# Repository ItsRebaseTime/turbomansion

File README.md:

# turbomansion

Hello, welcome to the turbomansion repository.

## The name

First let's start with the name - turbomansion.
The word comes from a few places in pop culture history but for me it got stuck in my head because of the legendary looter-shooter video game series - Borderlands, made by 2K and Gearbox. "Turbomansion" is mentioned in Borderlands The Pre-Sequel during mission "Lost Legion Invasion" as seen in this [video](https://www.youtube.com/watch?v=5qd0URBWsjE).

## The idea

Main goal of this project is to create a fully open source smart home units library. Of course nothing is perfect and so is this project, some things may deviate from the ultimate goal and some compromises will be made but I will be happy and I hope anyone who reads this would feel the same if the project does not deviate too far from these values:

* Open source documentation, plans, files, code, etc.
* Easily obtainable materials all over the world
* Low cost and low effort
* Ease of deployment
* Ease of use
* Ease of maintenance and repair
* Customizability
* No proprietary bullshit
* No manufacturer cloud connectivity (unless you want to (trust me - you don't))
* Complete control with Home Assistant

## Units

### Multisensor

[Multisensor](/units/multisensor/README.md) - An all-in-one solution for your home monitoring and automation needs.

### Control panel

[Control panel](/units/control_panel/README.md) - An awesome home automation dashboard/control panel.

### PoE roller blinds

[PoE roller blinds](/units/roller_blinds/README.md) - Smart and automated PoE powered roller blinds.

### DT82TV curtain motor controller

[DT82TV curtain motor controller](/units/rs485_dooya_curtain_controller/README.md) - RS485 controller setup for Dooya DT82TV curtain motors with ESPHome.

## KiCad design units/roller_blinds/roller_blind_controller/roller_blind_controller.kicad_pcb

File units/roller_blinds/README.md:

# PoE Roller Blinds

## Introduction

During my smart home development I was searching for smart PoE-powered black-out roller blinds and to my surprise I was not able to find anything remotely affordable and compatible with my home assistant setup.

There are a few offerings in the industry but they have their own downsides:

| Product                                                                                                                         | Features                                                                                                                 | Antifeatures                                                                                                                                         |
|---------------------------------------------------------------------------------------------------------------------------------|--------------------------------------------------------------------------------------------------------------------------|------------------------------------------------------------------------------------------------------------------------------------------------------|
| [Powershades TruePoE](https://powershades.com/truepoe)                                                                          | All-in-one solution, easy to deploy                                                                                      | Cloud-based, unrepairable (no available parts), not sold in EU                                                                                       |
| [Somfy Sonesse® 30 PoE (and other variations)](https://www.somfysystems.com/en-us/products/1241147/sonesse-30-poe)              | All-in-one solution, easy to deploy                                                                                      | Too expensive (400 eur), unrepairable (no available parts), proprietary control interface                                                            |
| [Smart wings hardwired PoE roller blinds](https://www.smartwingshome.com/pages/the-worlds-first-poe-matter-over-ethernet-motor) | All-in-one solution, easy to deploy, optional PoE and DC power, compatible with Home Assistant and Matter out of the box | The motor itself is 170eur, unrepairable (no available parts), but it is still the best solution if you want plug and play PoE powered roller blinds |

## Features

| Feature      | Specifications                                                      | Note     |
|--------------|---------------------------------------------------------------------|----------|
| PoE          | 802.3af, 6W                                                         |          |
| Ethernet     | 802.3-2008, 10/100Mbps                                              |          |
| WiFi         | 802.11b/g/n, 150Mbps                                                | Optional |
| Bluetooth    | Bluetooth v4.2 BR/EDR and Bluetooth LE                              | Optional |
| Motor driver | TMC2209, silent, sensor-less homing, speed and acceleration control |          |

## Main parts

| Part                                      | Datasheet                                                                   | EU Shop                                                                                                         |
|-------------------------------------------|-----------------------------------------------------------------------------|-----------------------------------------------------------------------------------------------------------------|
| M5Stack PoE ESP32                         | [link](/units/roller_blinds/assets/docs/poesp32.pdf)                        | [link](https://eu.mouser.com/ProductDetail/M5Stack/U138?qs=vvQtp7zwQdPAxf%252BUv9YNIg%3D%3D)                    |
| FYSETC TMC2209 V3/V4 stepper motor driver | [link](/units/roller_blinds/assets/docs/Silent2209%20-%20FYSETC%20WIKI.pdf) | [link](https://www.amazon.de/-/en/Printer-Upgrade-Microsteps-Motherboard-Controller/dp/B07Z8QP8M9/ref=sr_1_3)   |
| 2.54mm female header kit                  |                                                                             | [link](https://www.amazon.de/-/en/Straight-Connector-Assortment-Arduino-Prototype/dp/B07Q1XBGFB/ref=sr_1_2)     |
| M3 screw kit                              |                                                                             | [link](https://www.amazon.de/-/en/Countersunk-Stainless-Phillips-Assortment-Threaded/dp/B0DPKYXVWY/ref=sr_1_15) |
| M4 screw kit                              |                                                                             | [link](https://www.amazon.de/-/en/Countersunk-Stainless-Phillips-Assortment-Threaded/dp/B0DPL17F6X/ref=sr_1_15) |
| 8x2 round magnets                         |                                                                             | [link](https://www.amazon.de/-/en/Aenienoe-Magnets-Neodymium-Magnetic-Whiteboard/dp/B0DDBQJ7TM/ref=sr_1_5)      |

## 3D printed parts

| Part                | File                                                                          | Note                                                                                          |
|---------------------|-------------------------------------------------------------------------------|-----------------------------------------------------------------------------------------------|
| Motor mount         | [file](/units/roller_blinds/assets/cad_files/for_printing/28byj-48_mount.3mf) | Holds the motor                                                                               |
| Spring mount        | [file](/units/roller_blinds/assets/cad_files/for_printing/spring_mount.3mf)   | Holds the spring assembly                                                                     |
| Motor shaft adapter | [file](/units/roller_blinds/assets/cad_files/for_printing/motor_adapter.3mf)  | Adapts the motor shaft to the aluminium extrusion of the roller blind                         |
| Motor cover         | [file](/units/roller_blinds/assets/cad_files/for_printing/motor_cover.3mf)    | Holds the electronics and can be used to cover up the other side too if you like the symmetry |

## Optional parts

| Part                                     | Datasheet                                                                     | EU Shop                                                                                                  | Note                                                |
|------------------------------------------|-------------------------------------------------------------------------------|----------------------------------------------------------------------------------------------------------|-----------------------------------------------------|
| 2.4GHz BT/Wifi flexible adhesive antenna | [link](/units/roller_blinds/assets/Amphenol_04262021_PIOV0MSNRBA-2306519.pdf) | [link](https://eu.mouser.com/ProductDetail/Amphenol-SAA/PIOV0MSNRBA-100?qs=GedFDFLaBXF5eAFxhrTnpw%3D%3D) | Can enable Bluetooth functionality for various uses |

## Electronics

The electronics assembly is based on M5Stack PoE ESP32 module:

When opened it will contain 2 PCBs connected via 2x5 pin header. The PCB with the RJ45 port and ESP32 module will be used as the main board for this project, the other PCB will be dismantled for the PoE module.

The complete assembly could be done with a perforated soldering board and a few wires, but since we do things proper-ish around here - the printed circuit board was designed:

## Motor preparation

The 28BYJ-48 unipolar motor is designed to be controlled with simpler logic, for example shift registers and contains the center taps of both of the coils connected to the 5th pin in the connector:

This makes the motor unusable with regular bipolar motor drivers like TMC2209. Luckily there is a simple modification to convert 28BYJ-48 to bipolar operation.

### The modification

You will need to take off the blue plastic cover from the side of the motor to reveal a small PCB with all the electrical connections of the motor. Then cut the center trace. I have done it with a rotary tool, but a sharp knife would work nicely too.

### Before

### After

Now the motor will work with any common stepper motor driver.

## Driver

The 28BYJ-48 motor is designed to take full 5V current on half of its coil. After the modification we technically doubled the coil resistance and can crank the TMC2209 driver current all the way up with the on-board potentiometer. I used FYSETC TMC2209 V4.0 driver boards so for me the potentiometer should be turned all the way clockwise.

> [!NOTE]
> If you are using any other TMC2209 driver - double check the RX, TX, INDEX, and DIAG pin positions, they differ from driver to driver and you may need to creatively add 1k resistor between RX and TX pins on the board. Also some of the boards have VREF, DIAG, and INDEX pins switched around. PCB only supports driver boards which have INDEX and DIAG pins at 90 degrees from the other pins.

## Electronics assembly

The complete electronics assembly looks like this:

## Mechanical assembly

And the complete mechanical assembly looks like this:

## ESPHome configuration

```
esphome:
  name: blinds
  friendly_name: Blinds
  on_boot:
    - tmc2209.configure:
        microsteps: 1
        interpolation: True
        enable_spreadcycle: False
        tcool_threshold: 1000 # SG can be triggered when speed exceeds this value
    - tmc2209.stallguard:
        threshold: 5 # SG is triggered if the SG value is lower than 2x threshold
    - tmc2209.currents:
        standstill_mode: normal # coil_short_ls
        irun: 31 # 16 for best microstep performance (16/32 = 1/2 maximum motor current)
        ihold: 16 # should be 0 to enable passive breaking
        tpowerdown: 0
        iholddelay: 0
    - button.press: home_button # home right after boot

esp32:
  board: esp32dev
  framework:
    type: arduino
    
# Enable logging
logger:
  hardware_uart: UART2

# Enable Home Assistant API
api:
  encryption:
    key: "xxxxxxxxxxxxxxxxxxxxxxxxxx"

ota:
  - platform: esphome
    password: "xxxxxxxxxxxxxxxxxxxxxxxxxxxxxxxxx"

ethernet:
  type: IP101
  mdc_pin: GPIO23
  mdio_pin: GPIO18
  clk_mode: GPIO0_IN
  phy_addr: 1
  power_pin: GPIO5

text_sensor:
  - platform: ethernet_info
    ip_address:
      name: "IP"
    mac_address:
      name: "MAC"
    dns_address:
      name: "DNS"

external_components:
  - source: github://slimcdk/esphome-custom-components
    components: [ tmc2209_hub, tmc2209, stepper ]

globals:
  - id: has_homed
    type: bool
    initial_value: "true"
    restore_value: False
  - id: blinds_bottom_pos
    type: int
    initial_value: '9999'
    restore_value: True
  - id: blinds_top_pos
    type: int
    initial_value: '0'
    restore_value: True

uart:
  id: tmc2209_uart
  rx_pin: GPIO1
  tx_pin: GPIO3
  baud_rate: 500000
  
tmc2209_hub:
  id: tmc_hub
  uart_id: tmc2209_uart

stepper:
  - platform: tmc2209
    id: driver
    tmc2209_hub_id: tmc_hub
    diag_pin: GPIO17
    index_pin: GPIO16
    max_speed: 50 steps/s
    acceleration: 20 steps/s^2
    deceleration: 20 steps/s^2
    address: 0x00
    # rsense: 110 mOhm
    vsense: False
    on_status:
      - logger.log:
          format: "Driver is reporting an update! (code %d)"
          args: ["code"]
      - if:
          condition:
            lambda: return code == tmc2209::DIAG_TRIGGERED;
          then:
            - logger.log: DIAG_TRIGGERED
      - if:
          condition:
            lambda: return code == tmc2209::DIAG_TRIGGER_CLEARED;
          then:
            - logger.log: DIAG_TRIGGER_CLEARED
      - if:
          condition:
            lambda: return code == tmc2209::RESET;
          then:
            - logger.log: RESET
      - if:
          condition:
            lambda: return code == tmc2209::RESET_CLEARED;
          then:
            - logger.log: RESET_CLEARED
      - if:
          condition:
            lambda: return code == tmc2209::DRIVER_ERROR;
          then:
            - logger.log: DRIVER_ERROR
      - if:
          condition:
            lambda: return code == tmc2209::DRIVER_ERROR_CLEARED;
          then:
            - logger.log: DRIVER_ERROR_CLEARED
      - if:
          condition:
            lambda: return code == tmc2209::CP_UNDERVOLTAGE;
          then:
            - logger.log: CP_UNDERVOLTAGE
      - if:
          condition:
            lambda: return code == tmc2209::CP_UNDERVOLTAGE_CLEARED;
          then:
            - logger.log: CP_UNDERVOLTAGE_CLEARED
      - if:
          condition:
            lambda: return code == tmc2209::OVERTEMPERATURE_PREWARNING;
          then:
            - logger.log: OVERTEMPERATURE_PREWARNING
      - if:
          condition:
            lambda: return code == tmc2209::OVERTEMPERATURE_PREWARNING_CLEARED;
          then:
            - logger.log: OVERTEMPERATURE_PREWARNING_CLEARED
      - if:
          condition:
            lambda: return code == tmc2209::OVERTEMPERATURE;
          then:
            - logger.log: OVERTEMPERATURE
      - if:
          condition:
            lambda: return code == tmc2209::OVERTEMPERATURE_CLEARED;
          then:
            - logger.log: OVERTEMPERATURE_CLEARED
      - if:
          condition:
            lambda: return code == tmc2209::TEMPERATURE_ABOVE_120C;
          then:
            - logger.log: TEMPERATURE_ABOVE_120C
      - if:
          condition:
            lambda: return code == tmc2209::TEMPERATURE_BELOW_120C;
          then:
            - logger.log: TEMPERATURE_BELOW_120C
      - if:
          condition:
            lambda: return code == tmc2209::TEMPERATURE_ABOVE_143C;
          then:
            - logger.log: TEMPERATURE_ABOVE_143C
      - if:
          condition:
            lambda: return code == tmc2209::TEMPERATURE_BELOW_143C;
          then:
            - logger.log: TEMPERATURE_BELOW_143C
      - if:
          condition:
            lambda: return code == tmc2209::TEMPERATURE_ABOVE_150C;
          then:
            - logger.log: TEMPERATURE_ABOVE_150C
      - if:
          condition:
            lambda: return code == tmc2209::TEMPERATURE_BELOW_150C;
          then:
            - logger.log: TEMPERATURE_BELOW_150C
      - if:
          condition:
            lambda: return code == tmc2209::TEMPERATURE_ABOVE_157C;
          then:
            - logger.log: TEMPERATURE_ABOVE_157C
      - if:
          condition:
            lambda: return code == tmc2209::TEMPERATURE_BELOW_157C;
          then:
            - logger.log: TEMPERATURE_BELOW_157C
      - if:
          condition:
            lambda: return code == tmc2209::OPEN_LOAD;
          then:
            - logger.log: OPEN_LOAD
      - if:
          condition:
            lambda: return code == tmc2209::OPEN_LOAD_CLEARED;
          then:
            - logger.log: OPEN_LOAD_CLEARED
      - if:
          condition:
            lambda: return code == tmc2209::OPEN_LOAD_A;
          then:
            - logger.log: OPEN_LOAD_A
      - if:
          condition:
            lambda: return code == tmc2209::OPEN_LOAD_A_CLEARED;
          then:
            - logger.log: OPEN_LOAD_A_CLEARED
      - if:
          condition:
            lambda: return code == tmc2209::OPEN_LOAD_B;
          then:
            - logger.log: OPEN_LOAD_B
      - if:
          condition:
            lambda: return code == tmc2209::OPEN_LOAD_B_CLEARED;
          then:
            - logger.log: OPEN_LOAD_B_CLEARED
      - if:
          condition:
            lambda: return code == tmc2209::LOW_SIDE_SHORT;
          then:
            - logger.log: LOW_SIDE_SHORT
      - if:
          condition:
            lambda: return code == tmc2209::LOW_SIDE_SHORT_CLEARED;
          then:
            - logger.log: LOW_SIDE_SHORT_CLEARED
      - if:
          condition:
            lambda: return code == tmc2209::LOW_SIDE_SHORT_A;
          then:
            - logger.log: LOW_SIDE_SHORT_A
      - if:
          condition:
            lambda: return code == tmc2209::LOW_SIDE_SHORT_A_CLEARED;
          then:
            - logger.log: LOW_SIDE_SHORT_A_CLEARED
      - if:
          condition:
            lambda: return code == tmc2209::LOW_SIDE_SHORT_B;
          then:
            - logger.log: LOW_SIDE_SHORT_B
      - if:
          condition:
            lambda: return code == tmc2209::LOW_SIDE_SHORT_B_CLEARED;
          then:
            - logger.log: LOW_SIDE_SHORT_B_CLEARED
      - if:
          condition:
            lambda: return code == tmc2209::GROUND_SHORT;
          then:
            - logger.log: GROUND_SHORT
      - if:
          condition:
            lambda: return code == tmc2209::GROUND_SHORT_CLEARED;
          then:
            - logger.log: GROUND_SHORT_CLEARED
      - if:
          condition:
            lambda: return code == tmc2209::GROUND_SHORT_A;
          then:
            - logger.log: GROUND_SHORT_A
      - if:
          condition:
            lambda: return code == tmc2209::GROUND_SHORT_A_CLEARED;
          then:
            - logger.log: GROUND_SHORT_A_CLEARED
      - if:
          condition:
            lambda: return code == tmc2209::GROUND_SHORT_B;
          then:
            - logger.log: GROUND_SHORT_B
      - if:
          condition:
            lambda: return code == tmc2209::GROUND_SHORT_B_CLEARED;
          then:
            - logger.log: GROUND_SHORT_B_CLEARED
    on_stall:
      - logger.log: "Motor stalled!"
      - if:
          condition:
            lambda: |-
              return !id(has_homed);
          then:
            - stepper.stop: driver
            - stepper.report_position:
                id: driver
                position: 0
            - stepper.set_target:
                id: driver
                target: 0
            - globals.set:
                id: has_homed
                value: "true"
            - logger.log: "Homed"

button:
  - platform: template
    entity_category: DIAGNOSTIC
    id: home_button
    name: "Home"
    on_press:
      - logger.log: "Going home!"
      - globals.set:
          id: has_homed
          value: "false"
      - stepper.set_target:
          id: driver
          target: -9999999

  - platform: template
    entity_category: DIAGNOSTIC
    id: set_bottom_pos_button
    name: "Set bottom position"
    on_press:
      then:
        - globals.set: 
            id: blinds_bottom_pos
            value: !lambda 'return id(driver)->current_position;'
        - lambda: |-
            ESP_LOGD("Blinds", "Setting bottom position to: %d", id(driver)->current_position);

  - platform: template
    entity_category: DIAGNOSTIC
    id: set_top_pos_button
    name: "Set top position"
    on_press:
      then:
        - globals.set: 
            id: blinds_top_pos
            value: !lambda 'return id(driver)->current_position;'
        - lambda: |-
            ESP_LOGD("Blinds", "Setting top position to: %d", id(driver)->current_position);

  - platform: template
    entity_category: DIAGNOSTIC
    name: "10 Steps forward"
    on_press:
      - stepper.set_target:
          id: driver
          target: !lambda 'return id(driver)->current_position +10;'

  - platform: template
    entity_category: DIAGNOSTIC
    name: "10 Steps backward"
    on_press:
      - stepper.set_target:
          id: driver
          target: !lambda 'return id(driver)->current_position -10;'

  - platform: template
    entity_category: DIAGNOSTIC
    name: "100 Steps forward"
    on_press:
      - stepper.set_target:
          id: driver
          target: !lambda 'return id(driver)->current_position +100;'

  - platform: template
    entity_category: DIAGNOSTIC
    name: "100 Steps backward"
    on_press:
      - stepper.set_target:
          id: driver
          target: !lambda 'return id(driver)->current_position -100;'

  - platform: template
    entity_category: DIAGNOSTIC
    name: "1000 Steps forward"
    on_press:
      - stepper.set_target:
          id: driver
          target: !lambda 'return id(driver)->current_position +1000;'

  - platform: template
    entity_category: DIAGNOSTIC
    name: "1000 Steps backward"
    on_press:
      - stepper.set_target:
          id: driver
          target: !lambda 'return id(driver)->current_position -1000;'

  - platform: template
    name: Stop
    on_press:
      - stepper.stop: driver

  - platform: restart
    name: "Restart"

cover:
  - platform: template
    device_class: blind
    id: blinds
    name: "Blinds"
    optimistic: False
    has_position: True

    lambda: |-
      #define MAP_FLOAT(x, in_min, in_max, out_min, out_max) ((float)(x - in_min) * (out_max - out_min) / (float)(in_max - in_min) + out_min)
      return MAP_FLOAT(id(stepper_position_sensor)->state, id(blinds_top_pos), id(blinds_bottom_pos), 1.0, 0.0);
    open_action:
      - if:
          condition:
            lambda: |-
              return id(has_homed);
          then:
            - stepper.set_target: 
                id: driver
                target: !lambda 'return id(blinds_top_pos);'
    close_action:
      - if:
          condition:
            lambda: |-
              return id(has_homed);
          then:
            - stepper.set_target: 
                id: driver
                target: !lambda 'return id(blinds_bottom_pos);'
    stop_action: 
      then:
        - stepper.stop: driver
    position_action: 
      - if:
          condition:
            lambda: |-
              return id(has_homed);
          then:
            - stepper.set_target: 
                id: driver
                target: !lambda |-
                  #define MAP_FLOAT(x, in_min, in_max, out_min, out_max) ((float)(x - in_min) * (out_max - out_min) / (float)(in_max - in_min) + out_min)
                  int pos_to_set = MAP_FLOAT(pos, 0.0, 1.0, id(blinds_bottom_pos), id(blinds_top_pos));
                  ESP_LOGD("Blinds", "Rolling blinds to: %d (%f)", pos_to_set, pos);
                  return pos_to_set;
        
binary_sensor:
  - platform: template
    id: homed_status_sensor
    entity_category: DIAGNOSTIC
    name: "Homed status"
    lambda: |-
      return id(has_homed);

sensor:
  - platform: template
    entity_category: DIAGNOSTIC
    id: top_position_sensor
    name: "Top position"
    accuracy_decimals: 0
    unit_of_measurement: "steps"
    filters:
      - delta: 1
    lambda: |-
      return id(blinds_top_pos);

  - platform: template
    entity_category: DIAGNOSTIC
    id: bottom_position_sensor
    name: "Bottom position"
    accuracy_decimals: 0
    unit_of_measurement: "steps"
    filters:
      - delta: 1
    lambda: |-
      return id(blinds_bottom_pos);

  - platform: template
    entity_category: DIAGNOSTIC
    id: stepper_position_sensor
    name: "Position"
    unit_of_measurement: "steps"
    accuracy_decimals: 0
    update_interval: 1s
    filters:
      - delta: 1
    lambda: |-
      return id(driver)->current_position;

  - platform: tmc2209
    entity_category: DIAGNOSTIC
    internal: True
    type: stallguard_result
    name: Driver stallguard
    update_interval: 250ms
    filters:
      - delta: 1

  # - platform: tmc2209
  #   entity_category: DIAGNOSTIC
  #   type: motor_load
  #   name: Motor load
  #   update_interval: 250ms

  # - platform: tmc2209
  #   type: actual_current
  #   name: Actual current
  #   update_interval: 250ms

  # - platform: tmc2209
  #   type: pwm_scale_sum
  #   name: PWM Scale Sum
  #   update_interval: 250ms

  # - platform: tmc2209
  #   type: pwm_scale_auto
  #   name: PWM Scale Auto
  #   update_interval: 250ms

  # - platform: tmc2209
  #   type: pwm_ofs_auto
  #   name: PWM OFS Auto
  #   update_interval: 250ms

  # - platform: tmc2209
  #   type: pwm_grad_auto
  #   name: PWM Grad Auto
  #   update_interval: 250ms

```

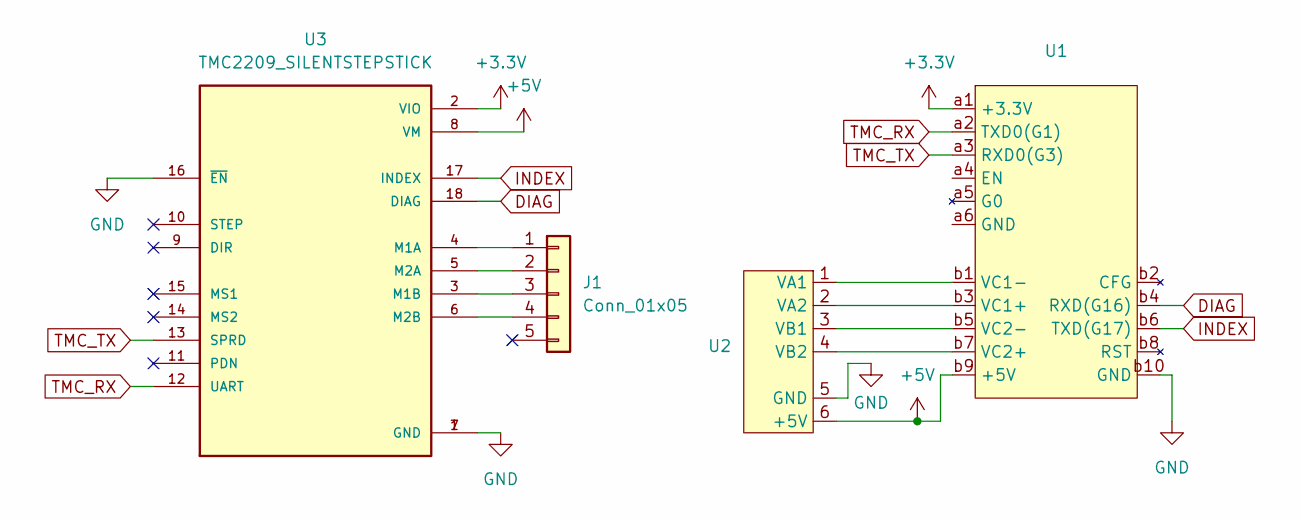
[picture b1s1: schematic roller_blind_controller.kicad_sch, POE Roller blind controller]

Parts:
J1: Conn_01x05; JST_XH_B5B-XH-A_1x05_P2.50mm_Vertical
U1: M5Stack_POE_base
U2: M5Stack_POE_module
U3: TMC2209_SILENTSTEPSTICK; MODULE_TMC2209_SILENTSTEPSTICK; PARTREV 1.20

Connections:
+3.3V: U1.a1 (+3.3V), U3.2 (VIO)
+5V: U1.b9 (+5V), U2.6 (+5V), U3.8 (VM)
DIAG: U1.b4 (RXD(G16)), U3.18 (DIAG)
GND: U1.b10 (GND), U2.5 (GND), U3.1 (GND), U3.7 (GND), U3.16 (~EN)
INDEX: U1.b6 (TXD(G17)), U3.17 (INDEX)
unnamed: J1.1, U3.4 (M1A)
unnamed: J1.2, U3.5 (M2A)
unnamed: J1.3, U3.3 (M1B)
unnamed: J1.4, U3.6 (M2B)
unnamed: U1.b3 (VC1+), U2.2 (VA2)
unnamed: U1.b1 (VC1-), U2.1 (VA1)
unnamed: U1.b7 (VC2+), U2.4 (VB2)
unnamed: U1.b5 (VC2-), U2.3 (VB1)
TMC_RX: U1.a2 (TXD0(G1)), U3.12 (UART)
TMC_TX: U1.a3 (RXD0(G3)), U3.13 (SPRD)

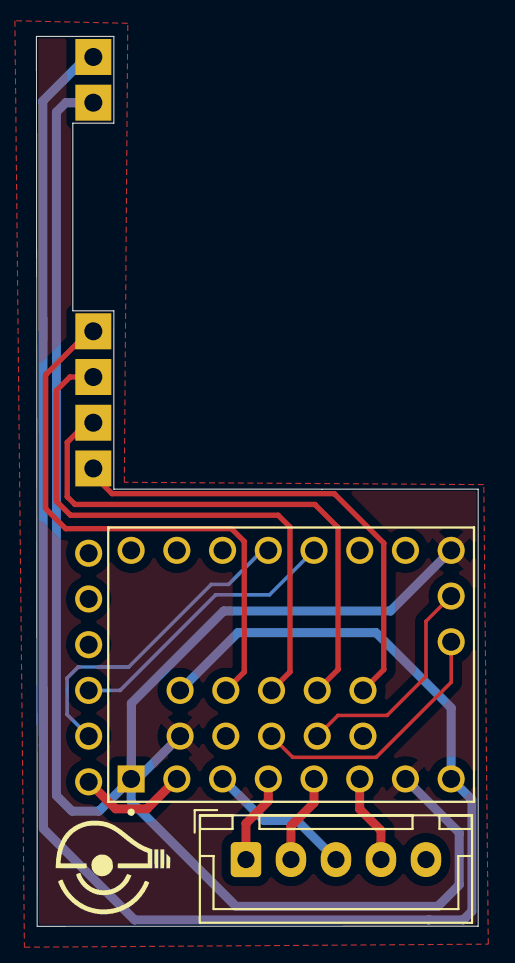
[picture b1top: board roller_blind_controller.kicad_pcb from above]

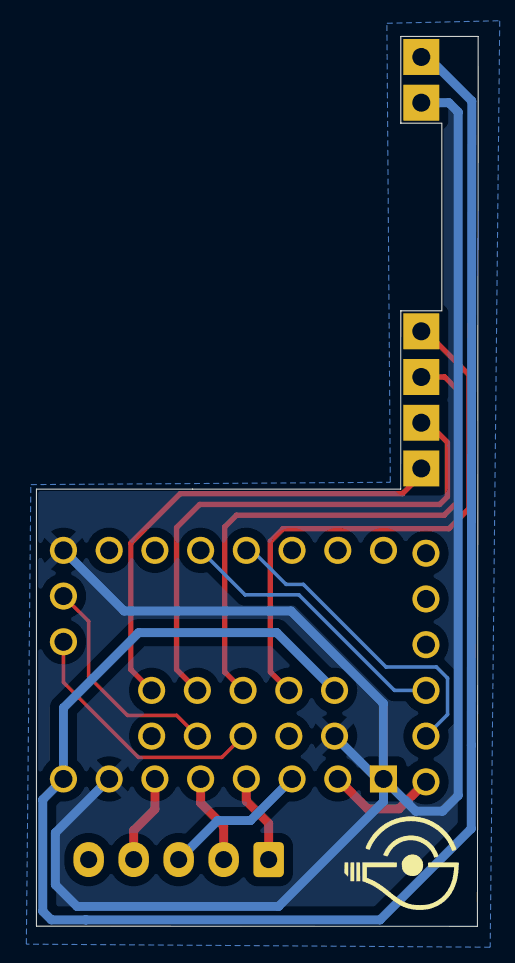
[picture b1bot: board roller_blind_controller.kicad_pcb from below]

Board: 2 copper layers, 24.5 x 49.4 mm, 4 parts (2 on the bottom side), 15 nets.

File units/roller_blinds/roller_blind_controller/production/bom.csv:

Designator,Footprint,Quantity,Value,LCSC Part #
J1,JST_XH_B5B-XH-A_1x05_P2.50mm_Vertical,1,Conn_01x05,
U1,M5Stack_POE_base,1,~,
U2,M5Stack_POE_module,1,~,
U3,MODULE_TMC2209_SILENTSTEPSTICK,1,TMC2209_SILENTSTEPSTICK,

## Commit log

2024-08-03 Add instructions for snapcast client
2024-10-26 POE modification and assembly steps
2024-11-30 add thermostat
2025-03-01 Add roller blinds docs and files
2025-03-01 Update main readme
2025-03-02 Update main readme and roller blind readme
2025-03-05 Update units
2025-03-05 Update roller blinds
2026-03-28 Add DT82TV motor controller
2026-03-28 Update yaml
